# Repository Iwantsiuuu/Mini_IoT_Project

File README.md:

This project mostly using ESP32 and ESP8266 for IoT microcontroller

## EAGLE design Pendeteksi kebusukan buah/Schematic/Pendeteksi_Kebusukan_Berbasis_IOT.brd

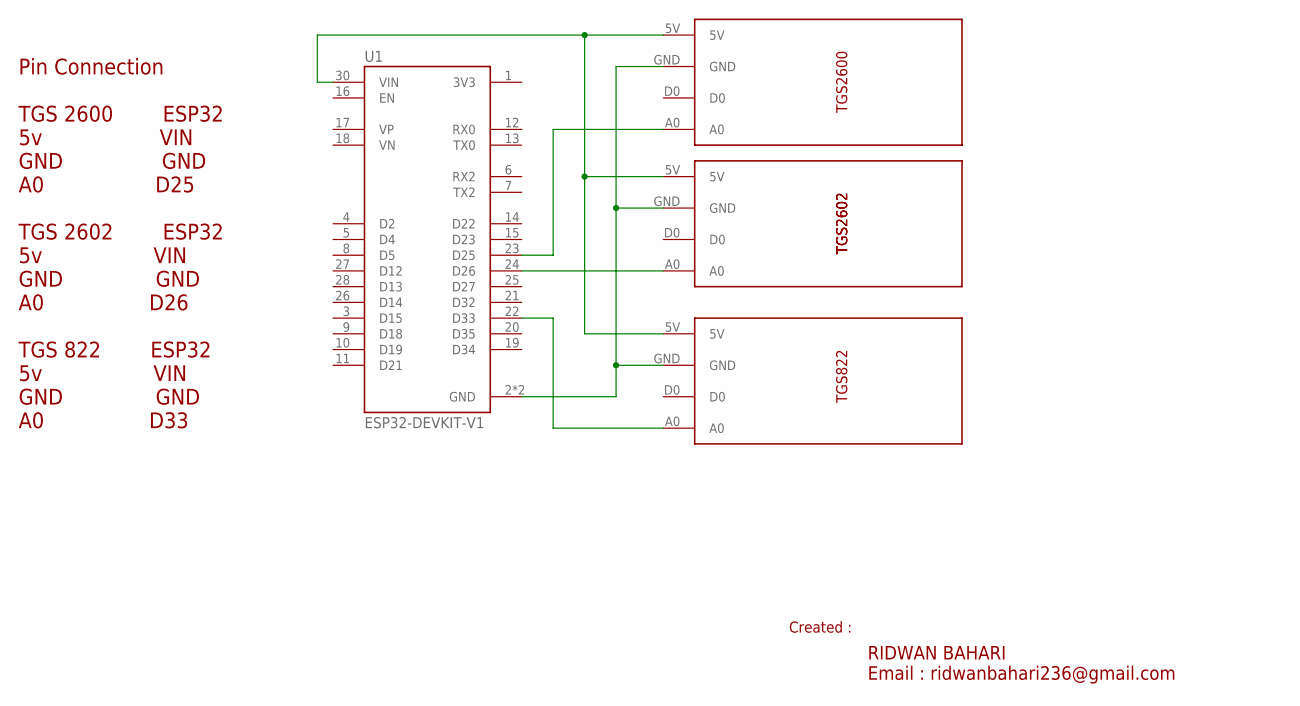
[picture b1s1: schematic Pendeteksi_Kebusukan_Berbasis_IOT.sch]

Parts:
SENSOR_GAS1, SENSOR_GAS2, SENSOR_GAS3: SENSOR_GAS
U1: ESP32-DEVKIT-V1; MODULE_ESP32_DEVKIT_V1

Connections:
unnamed: SENSOR_GAS1.5V, SENSOR_GAS2.5V, SENSOR_GAS3.5V, U1.30 (VIN)
unnamed: SENSOR_GAS1.GND, SENSOR_GAS2.GND, SENSOR_GAS3.GND, U1.2 (GND), U1.29 (GND)
unnamed: SENSOR_GAS1.A0, U1.23 (D25)
unnamed: SENSOR_GAS3.A0, U1.22 (D33)
unnamed: SENSOR_GAS2.A0, U1.24 (D26)

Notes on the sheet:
TGS2600
TGS2602
TGS822
Created :
RIDWAN BAHARI Email : ridwanbahari236@gmail.com
Pin Connection TGS 2600 ESP32 5v VIN GND GND A0 D25 TGS 2602 ESP32 5v VIN GND GND A0 D26 TGS 822 ESP32 5v VIN GND GND A0 D33

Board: 2 copper layers, 4 parts (0 on the bottom side), 5 nets, no tracks yet.

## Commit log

2024-07-08 Test1
2024-07-08 Add desible detection
2024-07-08 Add picture project
2024-07-08 Add code deteksi kebusukan
2024-07-13 Add electronics circuit connection
2024-07-14 Add new project
2024-08-03 Hallo
